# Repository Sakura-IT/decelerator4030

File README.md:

decelerator4030
===============

Decelerator 4030 CPU card for Amiga 3000/4000

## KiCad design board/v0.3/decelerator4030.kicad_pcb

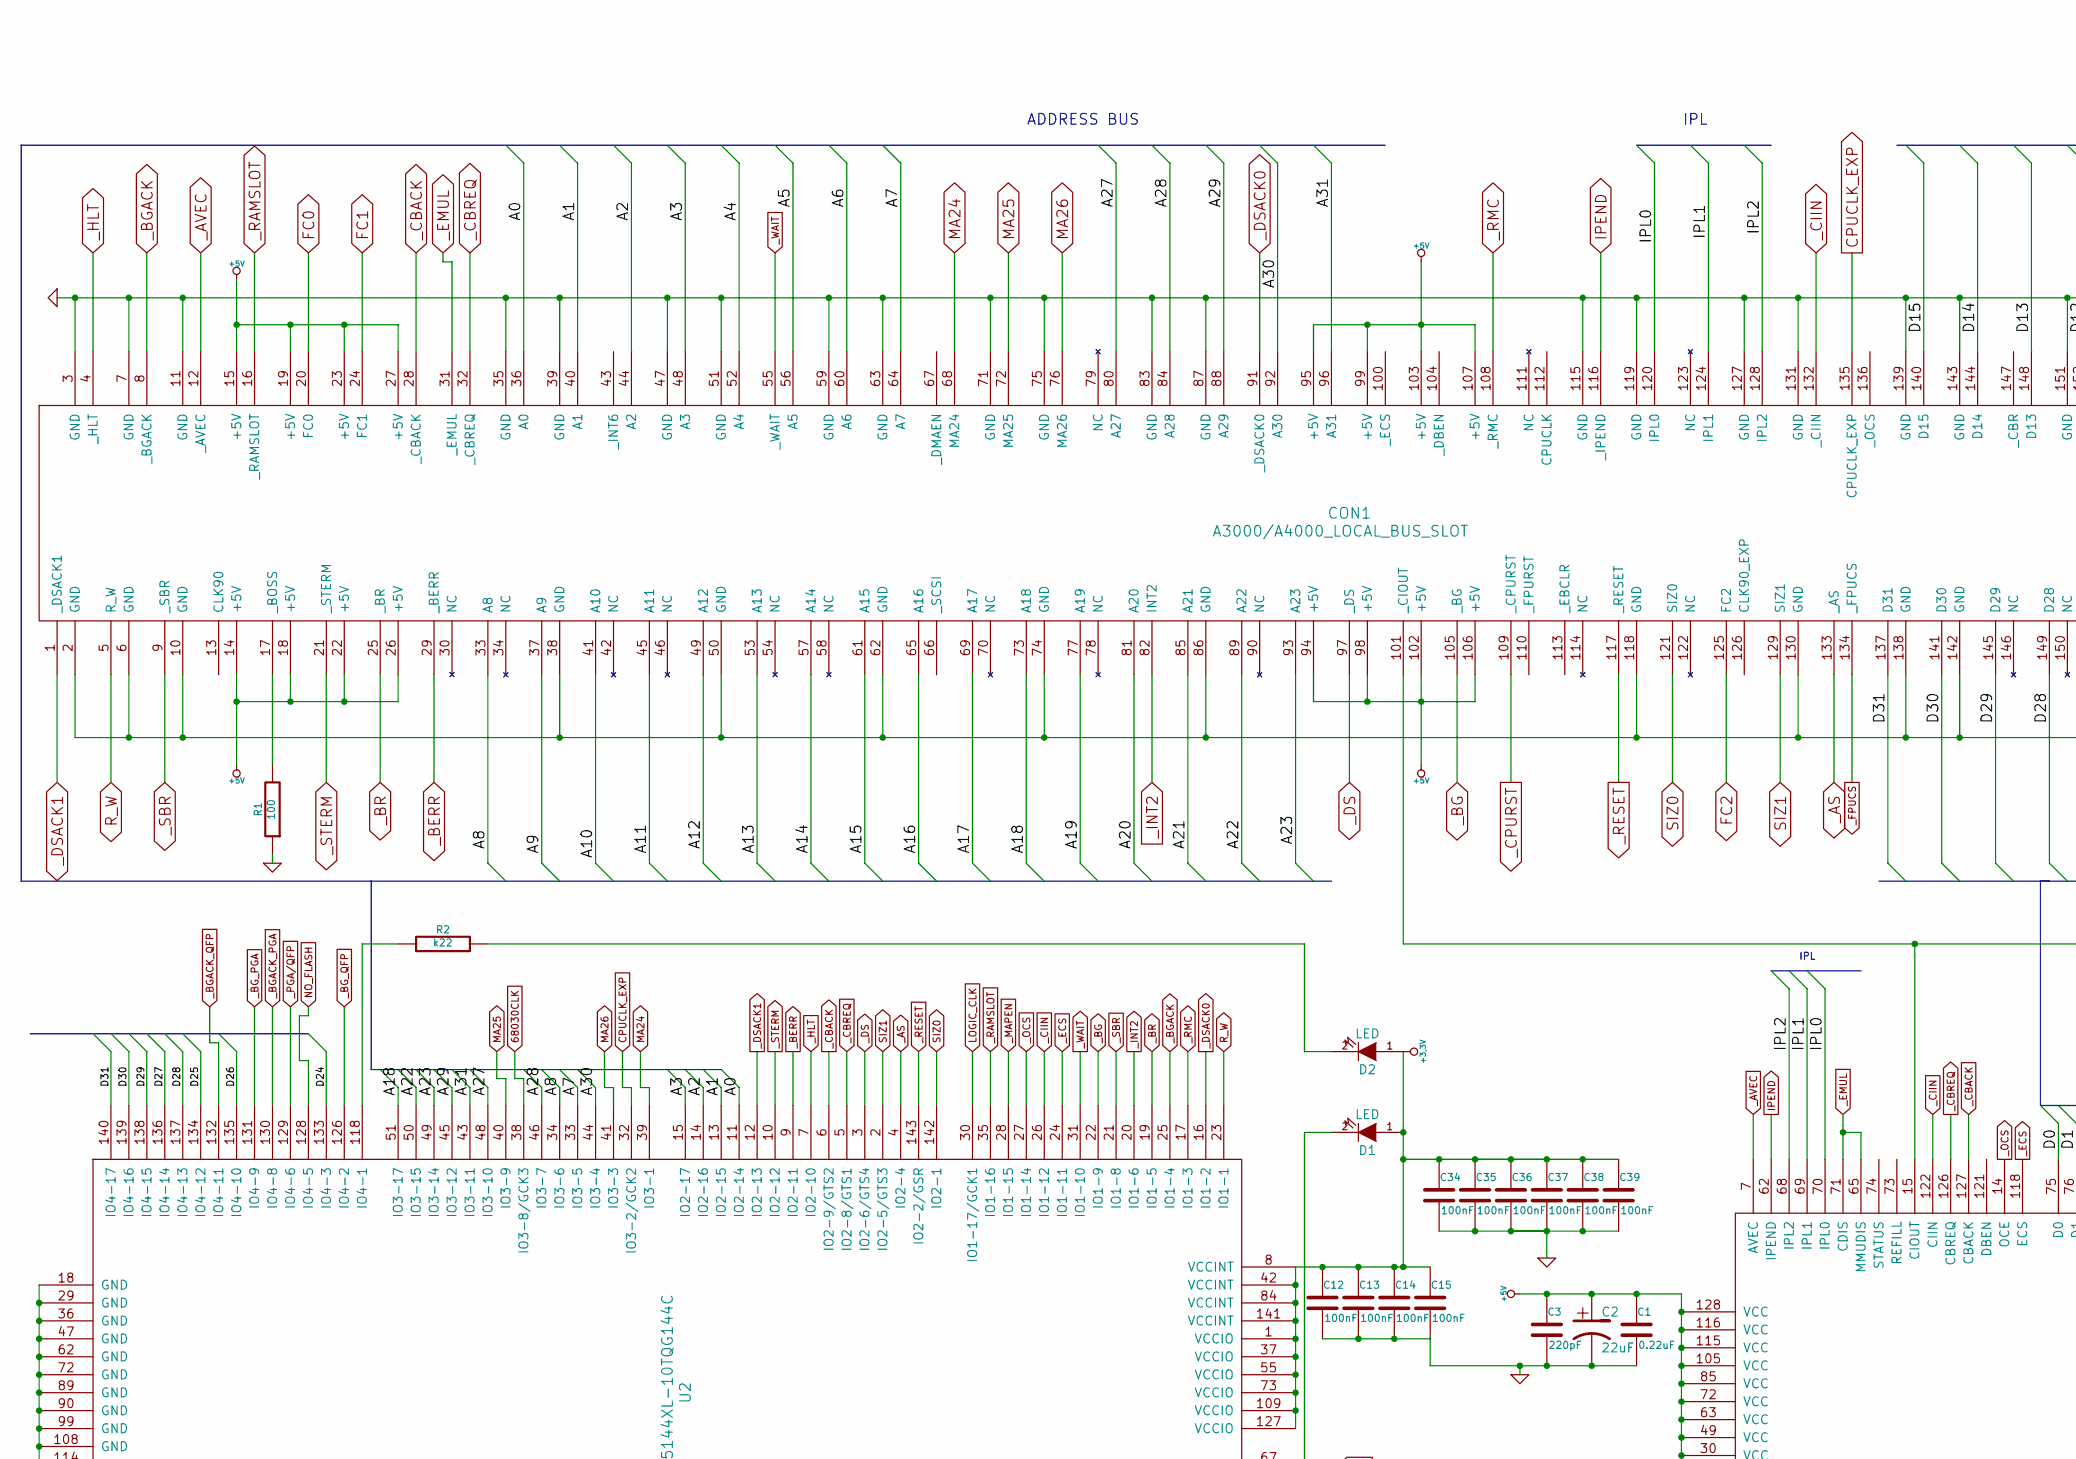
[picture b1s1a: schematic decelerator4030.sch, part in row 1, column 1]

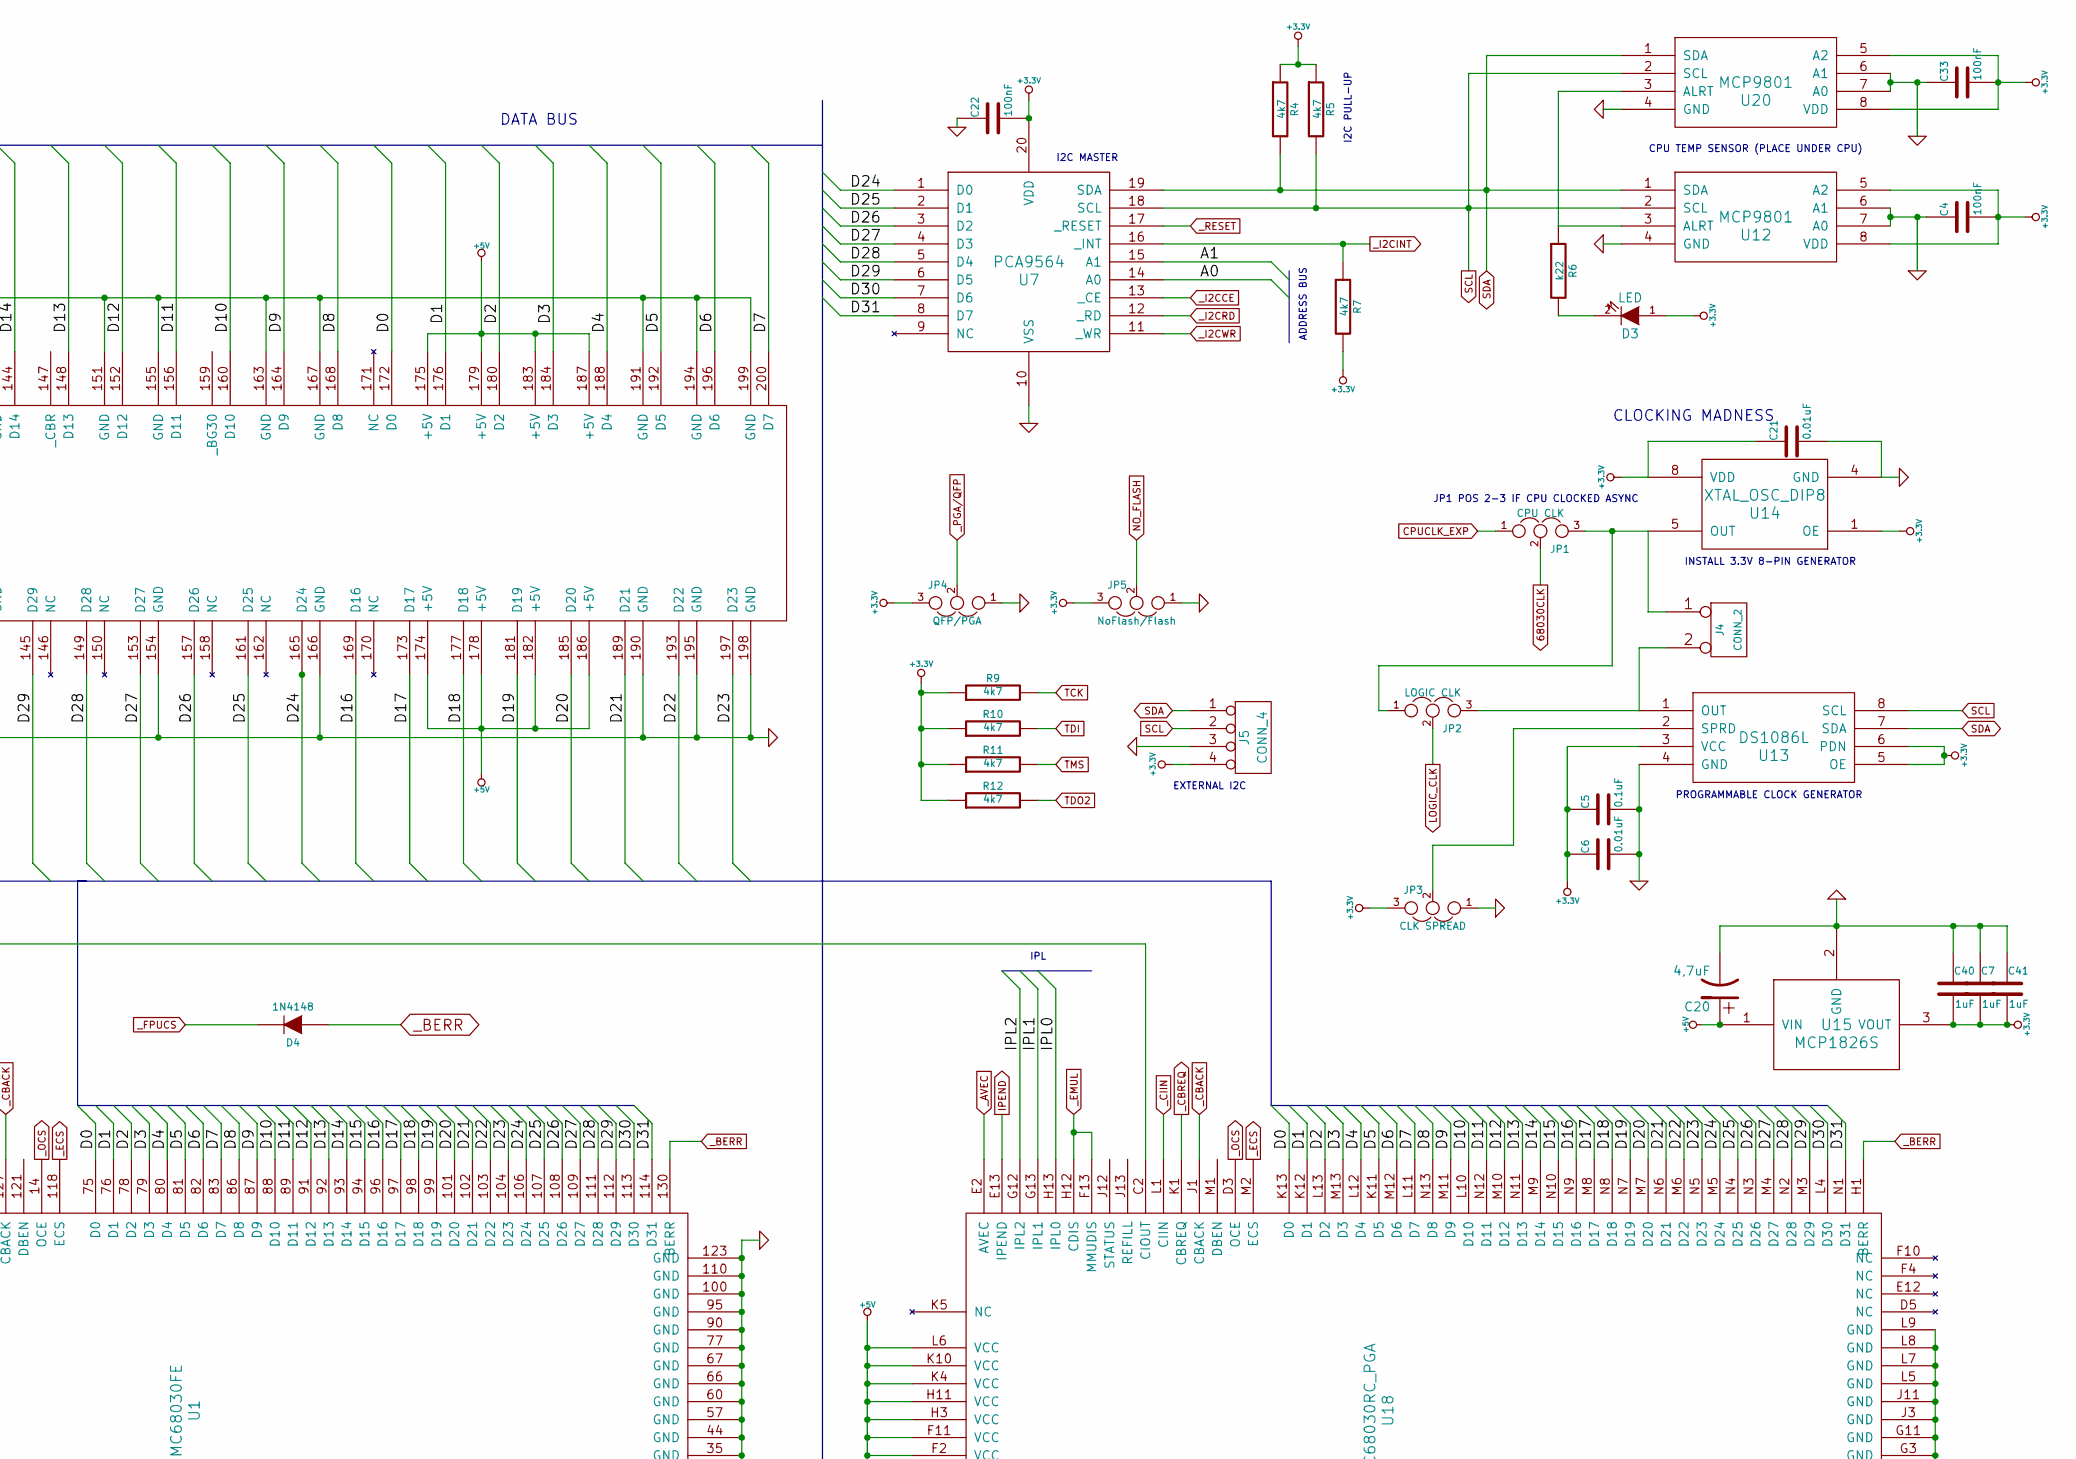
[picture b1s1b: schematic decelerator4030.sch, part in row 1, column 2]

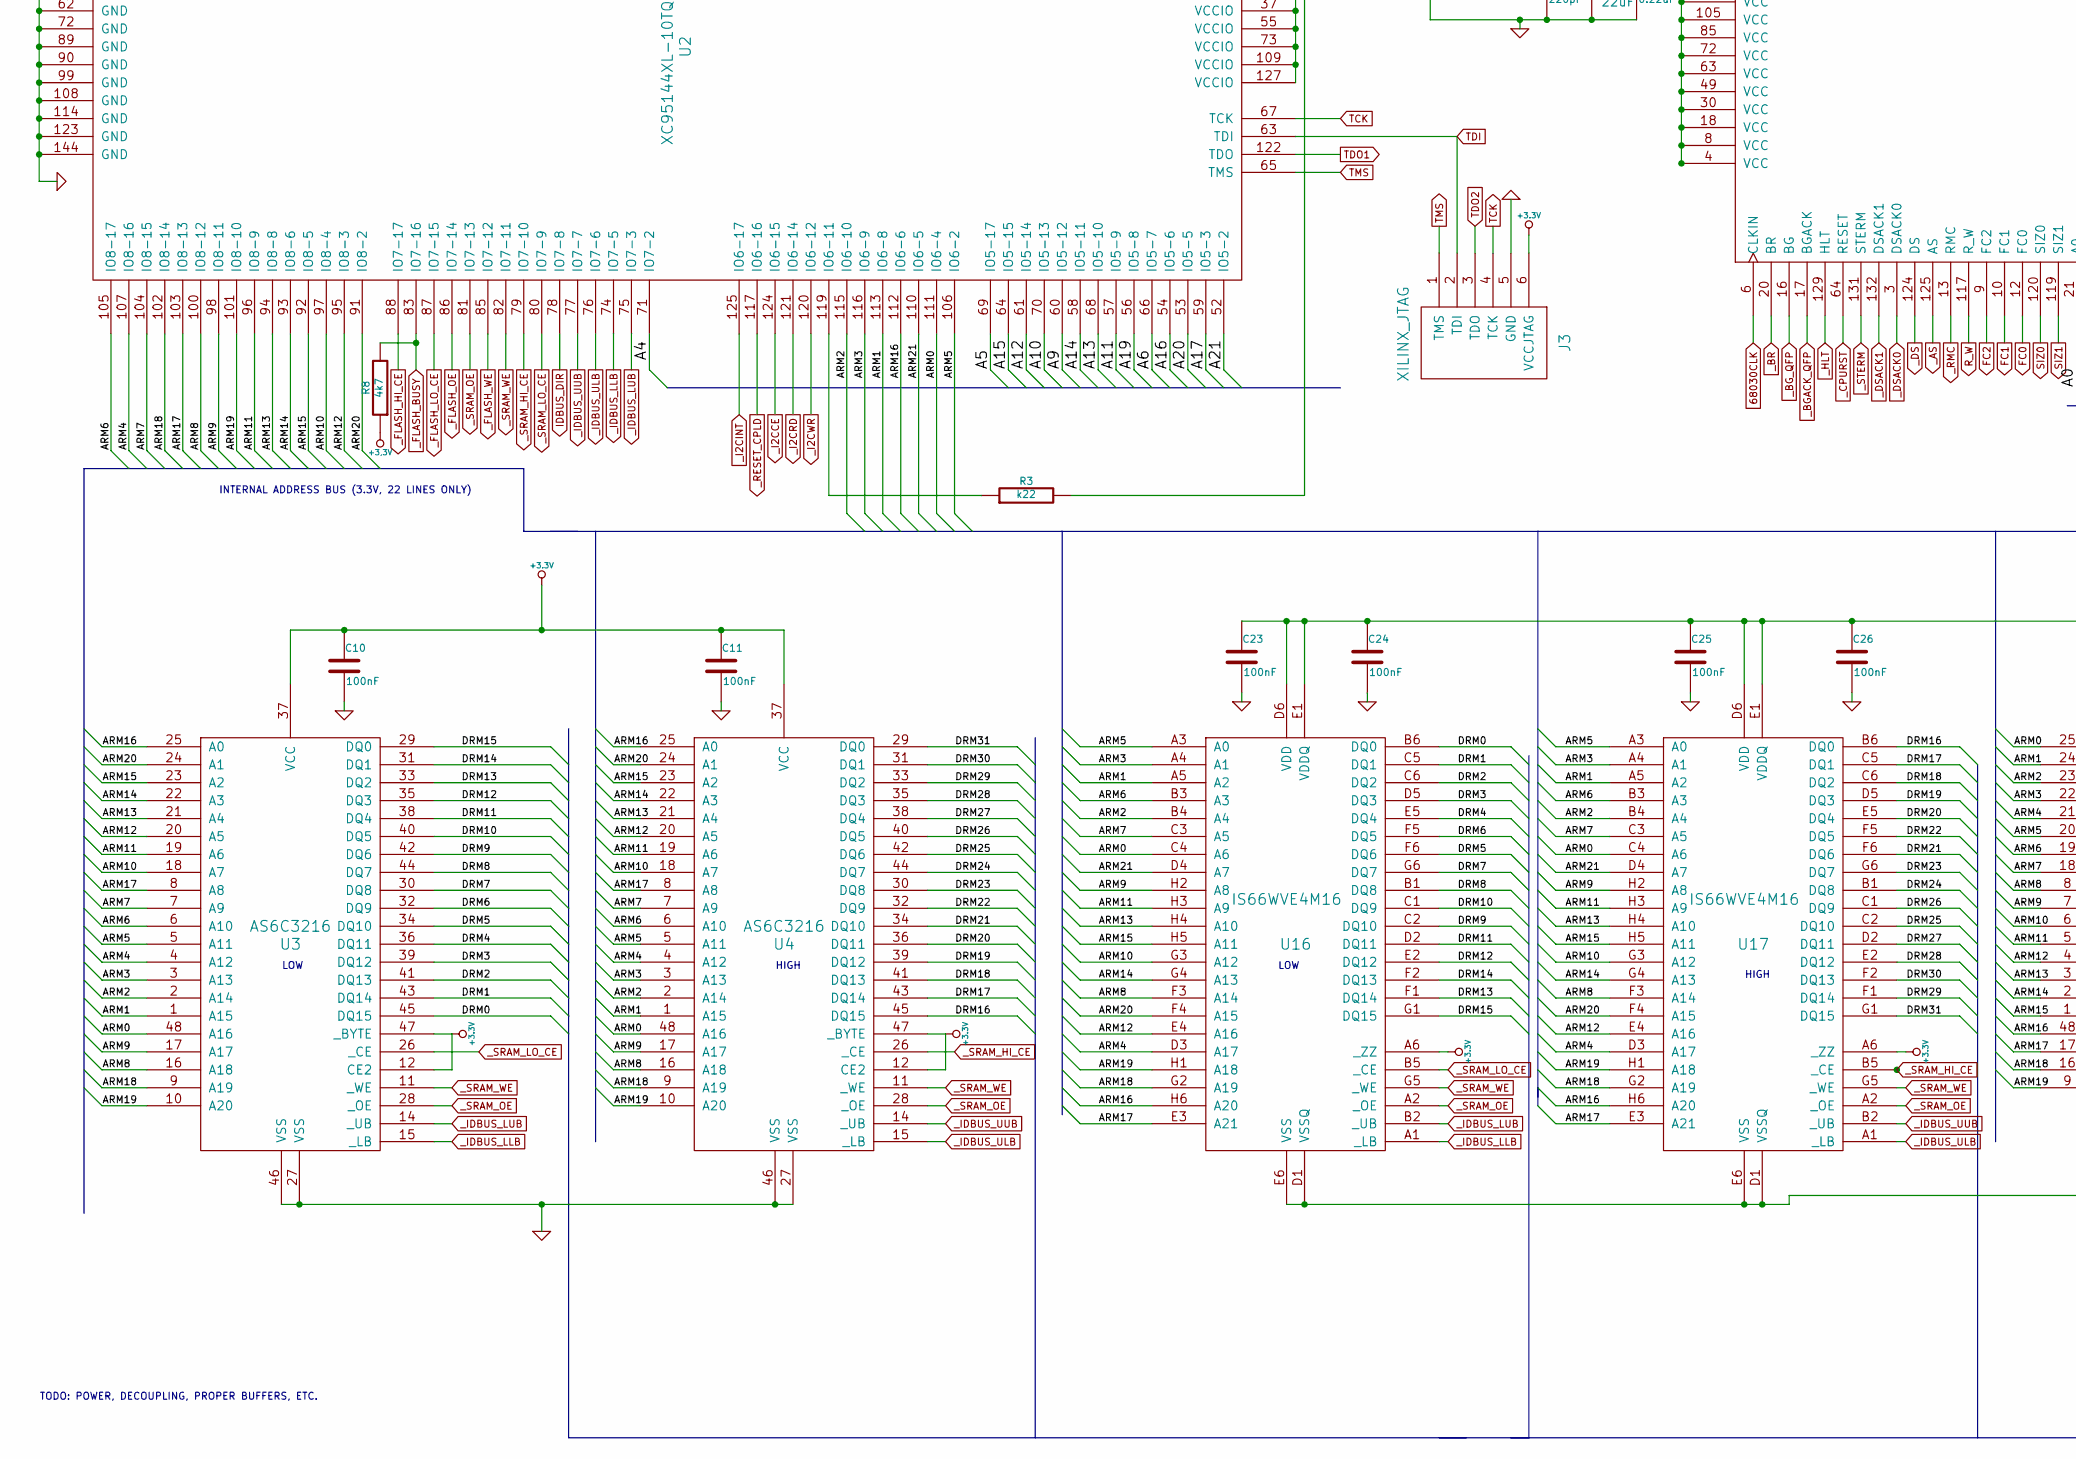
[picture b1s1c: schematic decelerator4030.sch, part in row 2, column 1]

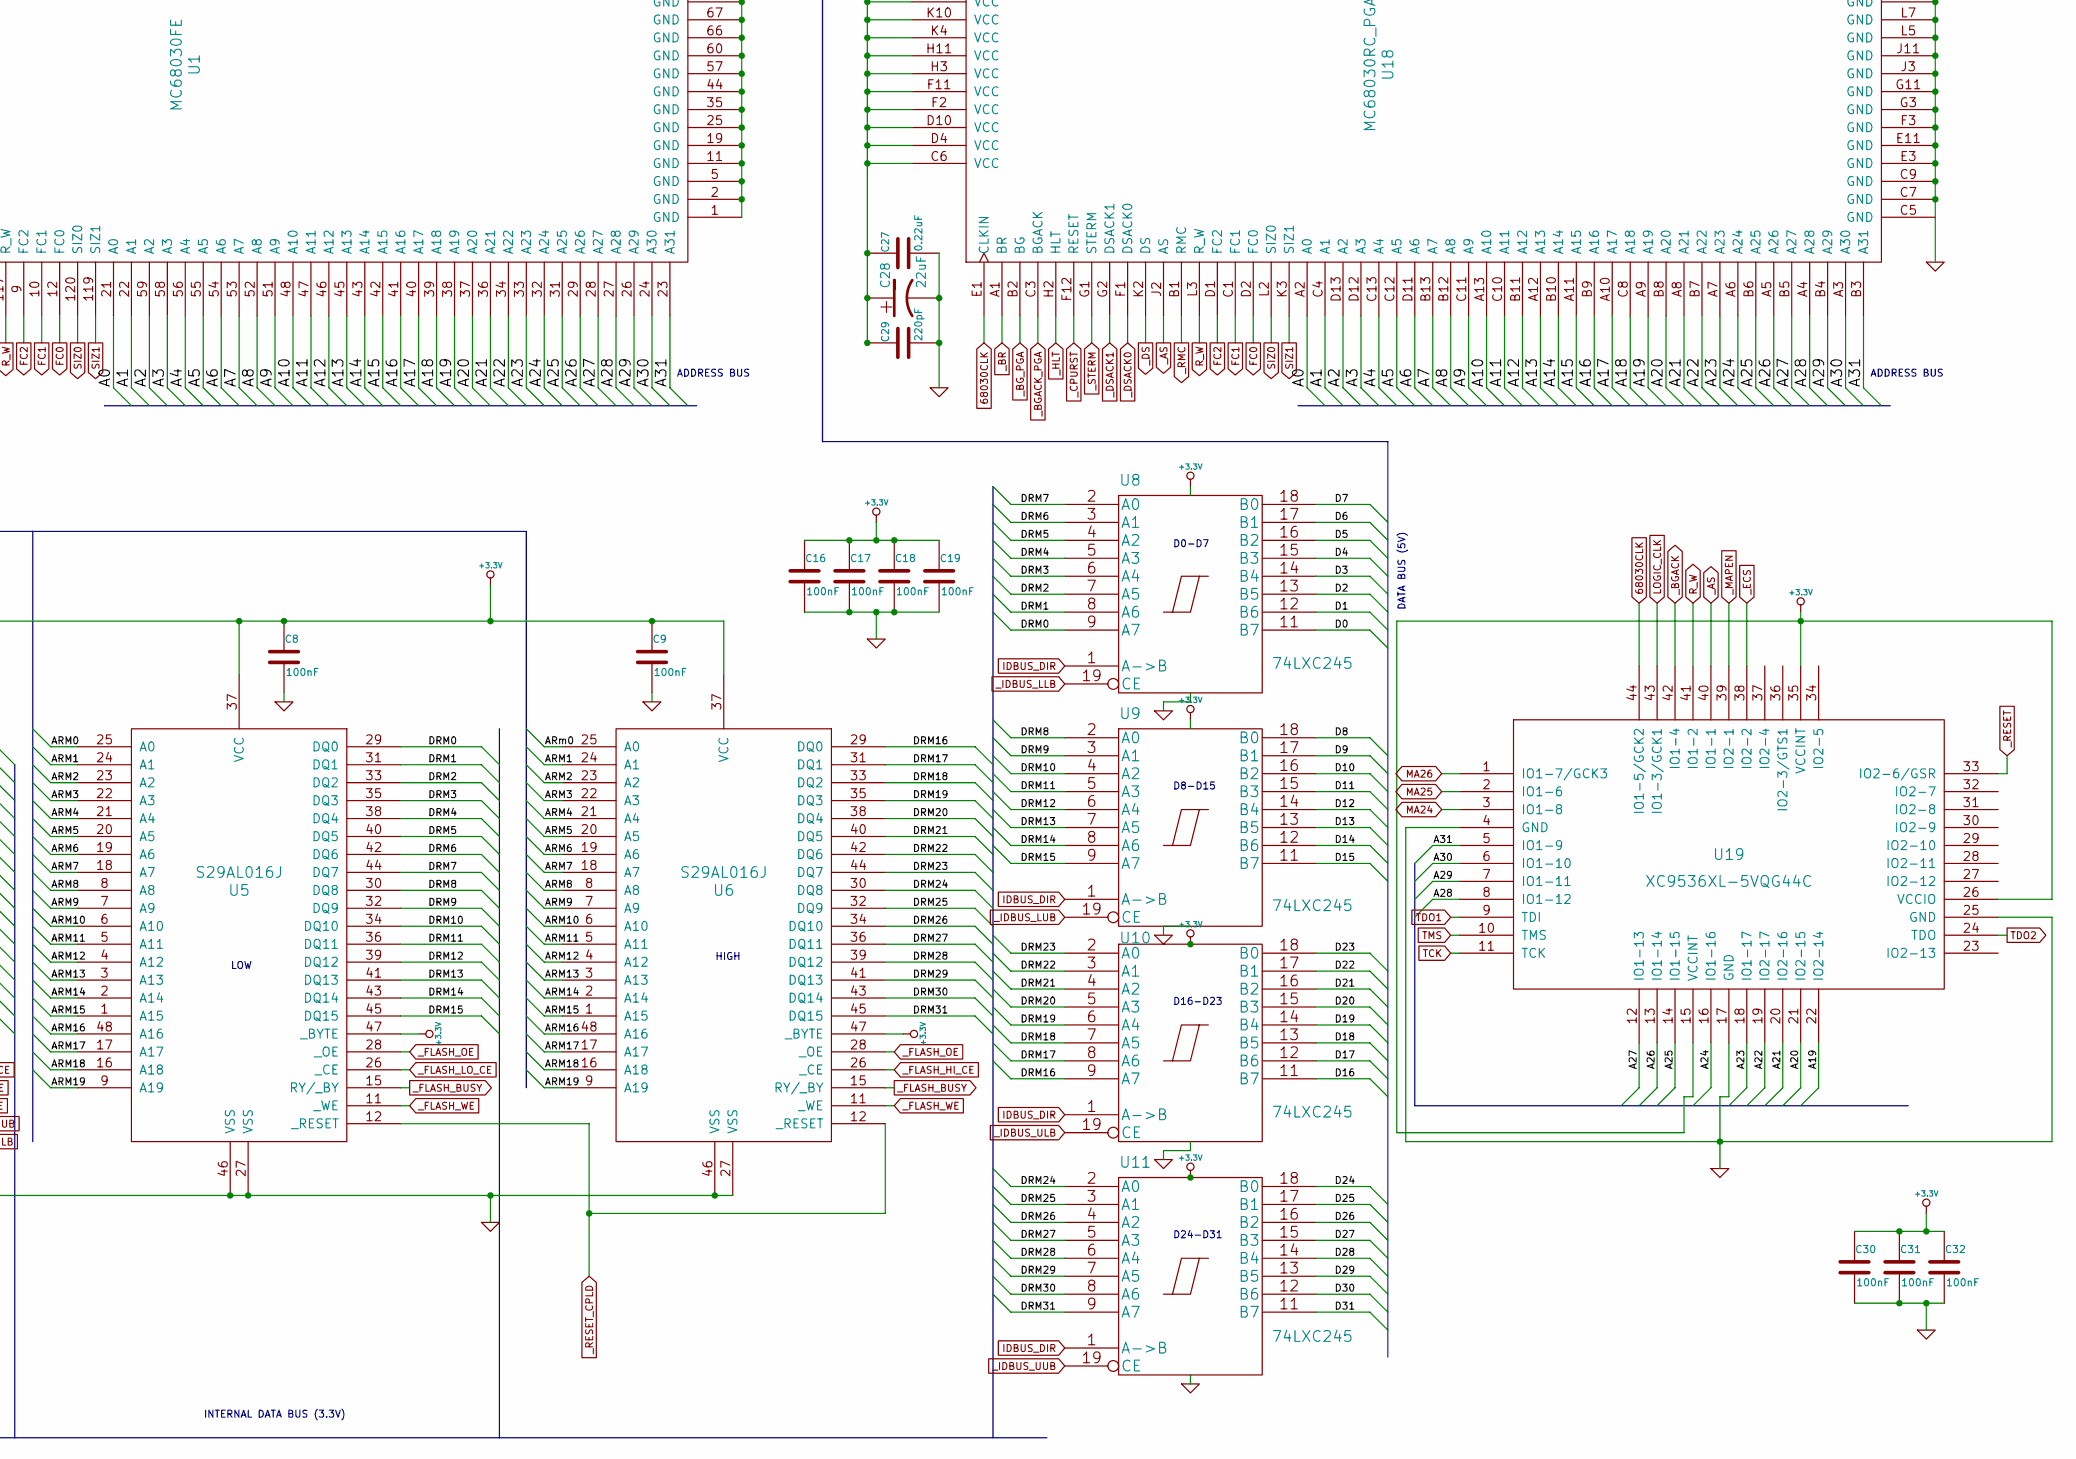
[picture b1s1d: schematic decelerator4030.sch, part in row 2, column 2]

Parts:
C1, C27: 0.22uF
C2, C28: 22uF
C3, C29: 220pF
C4, C8, C9, C10, C11, C12, C13, C14, C15, C16, C17, C18, C19, C22, C23, C24, C25, C26, C30, C31, C32, C33, C34, C35, C36, C37, C38, C39: 100nF
C5: 0.1uF
C6, C21: 0.01uF
C7, C40, C41: 1uF
C20: 4,7uF
CON1: A3000/A4000_LOCAL_BUS_SLOT
D1, D2, D3: LED
D4: 1N4148
J3: XILINX_JTAG
J4: CONN_2
J5: CONN_4
JP1: CPU CLK
JP2: LOGIC CLK
JP3: CLK SPREAD
JP4: QFP/PGA
JP5: NoFlash/Flash
R1: 100
R2, R3, R6: k22
R4, R5, R7, R8, R9, R10, R11, R12: 4k7
U1: MC68030FE
U2: XC95144XL-10TQG144C
U3, U4: AS6C3216
U5, U6: S29AL016J
U7: PCA9564
U8, U9, U10, U11: 74LXC245
U12, U20: MCP9801
U13: DS1086L
U14: XTAL_OSC_DIP8
U15: MCP1826S
U16, U17: IS66WVE4M16
U18: MC68030RC_PGA
U19: XC9536XL-5VQG44C

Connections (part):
68030CLK: JP1.2, U1.6 (CLKIN), U2.38 (IO3-8/GCK3), U18.E1 (CLKIN), U19.44 (IO1-5/GCK2)
+5V: C1.1, C2.1, C3.1, C20.1, C27.1, C28.1, C29.1, CON1.14 (+5V), CON1.15 (+5V), CON1.18 (+5V), CON1.19 (+5V), CON1.22 (+5V), CON1.23 (+5V), CON1.26 (+5V), CON1.27 (+5V), CON1.94 (+5V), CON1.95 (+5V), CON1.98 (+5V), CON1.99 (+5V), CON1.102 (+5V), CON1.103 (+5V), CON1.106 (+5V), CON1.107 (+5V), CON1.174 (+5V), CON1.175 (+5V), CON1.178 (+5V), CON1.179 (+5V), CON1.182 (+5V), CON1.183 (+5V), CON1.186 (+5V), CON1.187 (+5V), U1.4 (VCC), U1.8 (VCC), U1.18 (VCC), U1.30 (VCC), U1.49 (VCC), U1.63 (VCC), U1.72 (VCC), U1.85 (VCC), U1.105 (VCC), U1.115 (VCC), U1.116 (VCC), U1.128 (VCC), U15.1 (VIN), U18.C6 (VCC), U18.D4 (VCC), U18.D10 (VCC), U18.F2 (VCC), U18.F11 (VCC), U18.H3 (VCC), U18.H11 (VCC), U18.K4 (VCC), U18.K10 (VCC), U18.L6 (VCC)
/A0: CON1.36 (A0), U1.21 (A0), U2.11 (IO2-14), U7.14 (A0), U18.A2 (A0)
/A1: CON1.40 (A1), U1.22 (A1), U2.13 (IO2-15), U7.15 (A1), U18.C4 (A1)
/A2: CON1.44 (A2), U1.59 (A2), U2.14 (IO2-16), U18.D13 (A2)
/A3: CON1.48 (A3), U1.58 (A3), U2.15 (IO2-17), U18.D12 (A3)
/A4: CON1.52 (A4), U1.56 (A4), U2.71 (IO7-2), U18.C13 (A4)
/A5: CON1.56 (A5), U1.55 (A5), U2.69 (IO5-17), U18.C12 (A5)
/A6: CON1.60 (A6), U1.54 (A6), U2.66 (IO5-7), U18.D11 (A6)
/A7: CON1.64 (A7), U1.53 (A7), U2.33 (IO3-5), U18.B13 (A7)
/A8: CON1.33 (A8), U1.52 (A8), U2.34 (IO3-6), U18.B12 (A8)
/A9: CON1.37 (A9), U1.51 (A9), U2.60 (IO5-12), U18.C11 (A9)
/A10: CON1.41 (A10), U1.48 (A10), U2.70 (IO5-13), U18.A13 (A10)
/A11: CON1.45 (A11), U1.47 (A11), U2.57 (IO5-9), U18.C10 (A11)
/A12: CON1.49 (A12), U1.46 (A12), U2.61 (IO5-14), U18.B11 (A12)
/A13: CON1.53 (A13), U1.45 (A13), U2.68 (IO5-10), U18.A12 (A13)
/A14: CON1.57 (A14), U1.43 (A14), U2.58 (IO5-11), U18.B10 (A14)
/A15: CON1.61 (A15), U1.42 (A15), U2.64 (IO5-15), U18.A11 (A15)
/A16: CON1.65 (A16), U1.41 (A16), U2.54 (IO5-6), U18.B9 (A16)
/A17: CON1.69 (A17), U1.40 (A17), U2.59 (IO5-3), U18.A10 (A17)
/A18: CON1.73 (A18), U1.39 (A18), U2.51 (IO3-17), U18.C8 (A18)
/A19: CON1.77 (A19), U1.38 (A19), U2.56 (IO5-8), U18.A9 (A19), U19.22 (IO2-14)
/A20: CON1.81 (A20), U1.37 (A20), U2.53 (IO5-5), U18.B8 (A20), U19.21 (IO2-15)
/A21: CON1.85 (A21), U1.36 (A21), U2.52 (IO5-2), U18.A8 (A21), U19.20 (IO2-16)
/A22: CON1.89 (A22), U1.34 (A22), U2.50 (IO3-15), U18.B7 (A22), U19.19 (IO2-17)
/A23: CON1.93 (A23), U1.33 (A23), U2.49 (IO3-14), U18.A7 (A23), U19.18 (IO1-17)
/A24: U1.32 (A24), U18.A6 (A24), U19.16 (IO1-16)
/A25: U1.31 (A25), U18.B6 (A25), U19.14 (IO1-15)
/A26: U1.29 (A26), U18.A5 (A26), U19.13 (IO1-14)
/A27: CON1.80 (A27), U1.28 (A27), U2.48 (IO3-10), U18.B5 (A27), U19.12 (IO1-13)
/A28: CON1.84 (A28), U1.27 (A28), U2.46 (IO3-7), U18.A4 (A28), U19.8 (IO1-12)
/A29: CON1.88 (A29), U1.26 (A29), U2.45 (IO3-12), U18.B4 (A29), U19.7 (IO1-11)
/A30: CON1.92 (A30), U1.24 (A30), U2.44 (IO3-4), U18.A3 (A30), U19.6 (IO1-10)
/A31: CON1.96 (A31), U1.23 (A31), U2.43 (IO3-11), U18.B3 (A31), U19.5 (IO1-9)
/ARM0: U2.111 (IO6-4), U3.48 (A16), U4.48 (A16), U5.25 (A0), U6.25 (A0), U16.C4 (A6), U17.C4 (A6)
/ARM1: U2.113 (IO6-8), U3.1 (A15), U4.1 (A15), U5.24 (A1), U6.24 (A1), U16.A5 (A2), U17.A5 (A2)
/ARM2: U2.115 (IO6-10), U3.2 (A14), U4.2 (A14), U5.23 (A2), U6.23 (A2), U16.B4 (A4), U17.B4 (A4)
/ARM3: U2.116 (IO6-9), U3.3 (A13), U4.3 (A13), U5.22 (A3), U6.22 (A3), U16.A4 (A1), U17.A4 (A1)
/ARM4: U2.107 (IO8-16), U3.4 (A12), U4.4 (A12), U5.21 (A4), U6.21 (A4), U16.D3 (A17), U17.D3 (A17)
/ARM5: U2.106 (IO6-2), U3.5 (A11), U4.5 (A11), U5.20 (A5), U6.20 (A5), U16.A3 (A0), U17.A3 (A0)
/ARM6: U2.105 (IO8-17), U3.6 (A10), U4.6 (A10), U5.19 (A6), U6.19 (A6), U16.B3 (A3), U17.B3 (A3)
/ARM7: U2.104 (IO8-15), U3.7 (A9), U4.7 (A9), U5.18 (A7), U6.18 (A7), U16.C3 (A5), U17.C3 (A5)
/ARM8: U2.100 (IO8-12), U3.16 (A18), U4.16 (A18), U5.8 (A8), U6.8 (A8), U16.F3 (A14), U17.F3 (A14)
/ARM9: U2.98 (IO8-11), U3.17 (A17), U4.17 (A17), U5.7 (A9), U6.7 (A9), U16.H2 (A8), U17.H2 (A8)
/ARM10: U2.97 (IO8-4), U3.18 (A7), U4.18 (A7), U5.6 (A10), U6.6 (A10), U16.G3 (A12), U17.G3 (A12)
/ARM11: U2.96 (IO8-9), U3.19 (A6), U4.19 (A6), U5.5 (A11), U6.5 (A11), U16.H3 (A9), U17.H3 (A9)
/ARM12: U2.95 (IO8-3), U3.20 (A5), U4.20 (A5), U5.4 (A12), U6.4 (A12), U16.E4 (A16), U17.E4 (A16)
/ARM13: U2.94 (IO8-8), U3.21 (A4), U4.21 (A4), U5.3 (A13), U6.3 (A13), U16.H4 (A10), U17.H4 (A10)
/ARM14: U2.93 (IO8-6), U3.22 (A3), U4.22 (A3), U5.2 (A14), U6.2 (A14), U16.G4 (A13), U17.G4 (A13)
/ARM15: U2.92 (IO8-5), U3.23 (A2), U4.23 (A2), U5.1 (A15), U6.1 (A15), U16.H5 (A11), U17.H5 (A11)
/ARM16: U2.112 (IO6-6), U3.25 (A0), U4.25 (A0), U5.48 (A16), U6.48 (A16), U16.H6 (A20), U17.H6 (A20)
/ARM17: U2.103 (IO8-13), U3.8 (A8), U4.8 (A8), U5.17 (A17), U6.17 (A17), U16.E3 (A21), U17.E3 (A21)
/ARM18: U2.102 (IO8-14), U3.9 (A19), U4.9 (A19), U5.16 (A18), U6.16 (A18), U16.G2 (A19), U17.G2 (A19)
/ARM19: U2.101 (IO8-10), U3.10 (A20), U4.10 (A20), U5.9 (A19), U6.9 (A19), U16.H1 (A18), U17.H1 (A18)
/ARM20: U2.91 (IO8-2), U3.24 (A1), U4.24 (A1), U16.F4 (A15), U17.F4 (A15)
/ARM21: U2.110 (IO6-5), U16.D4 (A7), U17.D4 (A7)
/D0: CON1.172 (D0), U1.75 (D0), U8.11 (B7), U18.K13 (D0)
/D1: CON1.176 (D1), U1.76 (D1), U8.12 (B6), U18.K12 (D1)
/D2: CON1.180 (D2), U1.78 (D2), U8.13 (B5), U18.L13 (D2)
/D3: CON1.184 (D3), U1.79 (D3), U8.14 (B4), U18.M13 (D3)
/D4: CON1.188 (D4), U1.80 (D4), U8.15 (B3), U18.L12 (D4)
/D5: CON1.192 (D5), U1.81 (D5), U8.16 (B2), U18.K11 (D5)
/D6: CON1.196 (D6), U1.82 (D6), U8.17 (B1), U18.M12 (D6)
/D7: CON1.200 (D7), U1.83 (D7), U8.18 (B0), U18.L11 (D7)
/D8: CON1.168 (D8), U1.86 (D8), U9.18 (B0), U18.N13 (D8)
/D9: CON1.164 (D9), U1.87 (D9), U9.17 (B1), U18.M11 (D9)
/D10: CON1.160 (D10), U1.88 (D10), U9.16 (B2), U18.L10 (D10)
/D11: CON1.156 (D11), U1.89 (D11), U9.15 (B3), U18.N12 (D11)
/D12: CON1.152 (D12), U1.91 (D12), U9.14 (B4), U18.M10 (D12)
/D13: CON1.148 (D13), U1.92 (D13), U9.13 (B5), U18.N11 (D13)
/D14: CON1.144 (D14), U1.93 (D14), U9.12 (B6), U18.M9 (D14)
/D15: CON1.140 (D15), U1.94 (D15), U9.11 (B7), U18.N10 (D15)
/D16: CON1.169 (D16), U1.96 (D16), U10.11 (B7), U18.N9 (D16)
/D17: CON1.173 (D17), U1.97 (D17), U10.12 (B6), U18.M8 (D17)
/D18: CON1.177 (D18), U1.98 (D18), U10.13 (B5), U18.N8 (D18)
/D19: CON1.181 (D19), U1.99 (D19), U10.14 (B4), U18.N7 (D19)
/D20: CON1.185 (D20), U1.101 (D20), U10.15 (B3), U18.M7 (D20)
/D21: CON1.189 (D21), U1.102 (D21), U10.16 (B2), U18.N6 (D21)
/D22: CON1.193 (D22), U1.103 (D22), U10.17 (B1), U18.M6 (D22)
/D23: CON1.197 (D23), U1.104 (D23), U10.18 (B0), U18.N5 (D23)
/D24: CON1.165 (D24), U1.106 (D24), U2.133 (IO4-3), U7.1 (D0), U11.18 (B0), U18.M5 (D24)
/D25: CON1.161 (D25), U1.107 (D25), U2.134 (IO4-12), U7.2 (D1), U11.17 (B1), U18.N4 (D25)
/D26: CON1.157 (D26), U1.108 (D26), U2.135 (IO4-10), U7.3 (D2), U11.16 (B2), U18.N3 (D26)
/D27: CON1.153 (D27), U1.109 (D27), U2.136 (IO4-14), U7.4 (D3), U11.15 (B3), U18.M4 (D27)
/D28: CON1.149 (D28), U1.111 (D28), U2.137 (IO4-13), U7.5 (D4), U11.14 (B4), U18.N2 (D28)
/D29: CON1.145 (D29), U1.112 (D29), U2.138 (IO4-15), U7.6 (D5), U11.13 (B5), U18.M3 (D29)
/D30: CON1.141 (D30), U1.113 (D30), U2.139 (IO4-16), U7.7 (D6), U11.12 (B6), U18.L4 (D30)
/D31: CON1.137 (D31), U1.114 (D31), U2.140 (IO4-17), U7.8 (D7), U11.11 (B7), U18.N1 (D31)
/DRM0: U3.45 (DQ15), U5.29 (DQ0), U8.9 (A7), U16.B6 (DQ0)
/DRM1: U3.43 (DQ14), U5.31 (DQ1), U8.8 (A6), U16.C5 (DQ1)
/DRM2: U3.41 (DQ13), U5.33 (DQ2), U8.7 (A5), U16.C6 (DQ2)
/DRM3: U3.39 (DQ12), U5.35 (DQ3), U8.6 (A4), U16.D5 (DQ3)
/DRM4: U3.36 (DQ11), U5.38 (DQ4), U8.5 (A3), U16.E5 (DQ4)
/DRM5: U3.34 (DQ10), U5.40 (DQ5), U8.4 (A2), U16.F6 (DQ6)
/DRM6: U3.32 (DQ9), U5.42 (DQ6), U8.3 (A1), U16.F5 (DQ5)
/DRM7: U3.30 (DQ8), U5.44 (DQ7), U8.2 (A0), U16.G6 (DQ7)
/DRM8: U3.44 (DQ7), U5.30 (DQ8), U9.2 (A0), U16.B1 (DQ8)
/DRM9: U3.42 (DQ6), U5.32 (DQ9), U9.3 (A1), U16.C2 (DQ10)
/DRM10: U3.40 (DQ5), U5.34 (DQ10), U9.4 (A2), U16.C1 (DQ9)
/DRM11: U3.38 (DQ4), U5.36 (DQ11), U9.5 (A3), U16.D2 (DQ11)
/DRM12: U3.35 (DQ3), U5.39 (DQ12), U9.6 (A4), U16.E2 (DQ12)
/DRM13: U3.33 (DQ2), U5.41 (DQ13), U9.7 (A5), U16.F1 (DQ14)
/DRM14: U3.31 (DQ1), U5.43 (DQ14), U9.8 (A6), U16.F2 (DQ13)
/DRM15: U3.29 (DQ0), U5.45 (DQ15), U9.9 (A7), U16.G1 (DQ15)
/DRM16: U4.45 (DQ15), U6.29 (DQ0), U10.9 (A7), U17.B6 (DQ0)
/DRM17: U4.43 (DQ14), U6.31 (DQ1), U10.8 (A6), U17.C5 (DQ1)
/DRM18: U4.41 (DQ13), U6.33 (DQ2), U10.7 (A5), U17.C6 (DQ2)
/DRM19: U4.39 (DQ12), U6.35 (DQ3), U10.6 (A4), U17.D5 (DQ3)
/DRM20: U4.36 (DQ11), U6.38 (DQ4), U10.5 (A3), U17.E5 (DQ4)
/DRM21: U4.34 (DQ10), U6.40 (DQ5), U10.4 (A2), U17.F6 (DQ6)
/DRM22: U4.32 (DQ9), U6.42 (DQ6), U10.3 (A1), U17.F5 (DQ5)
/DRM23: U4.30 (DQ8), U6.44 (DQ7), U10.2 (A0), U17.G6 (DQ7)
/DRM24: U4.44 (DQ7), U6.30 (DQ8), U11.2 (A0), U17.B1 (DQ8)
/DRM25: U4.42 (DQ6), U6.32 (DQ9), U11.3 (A1), U17.C2 (DQ10)
/DRM26: U4.40 (DQ5), U6.34 (DQ10), U11.4 (A2), U17.C1 (DQ9)
/DRM27: U4.38 (DQ4), U6.36 (DQ11), U11.5 (A3), U17.D2 (DQ11)
/DRM28: U4.35 (DQ3), U6.39 (DQ12), U11.6 (A4), U17.E2 (DQ12)
/DRM29: U4.33 (DQ2), U6.41 (DQ13), U11.7 (A5), U17.F1 (DQ14)
/DRM30: U4.31 (DQ1), U6.43 (DQ14), U11.8 (A6), U17.F2 (DQ13)
/DRM31: U4.29 (DQ0), U6.45 (DQ15), U11.9 (A7), U17.G1 (DQ15)
/IPL0: CON1.120 (IPL0), U1.70 (IPL0), U18.H13 (IPL0)
/IPL1: CON1.124 (IPL1), U1.69 (IPL1), U18.G13 (IPL1)
/IPL2: CON1.128 (IPL2), U1.68 (IPL2), U18.G12 (IPL2)
CPUCLK_EXP: CON1.135 (CPUCLK_EXP), JP1.1, U2.32 (IO3-2/GCK2)
FC0: CON1.20 (FC0), U1.12 (FC0), U18.D2 (FC0)
FC1: CON1.24 (FC1), U1.10 (FC1), U18.C1 (FC1)
FC2: CON1.125 (FC2), U1.9 (FC2), U18.D1 (FC2)
GND: C1.2, C2.2, C3.2, C4.1, C5.2, C6.2, C7.1, C8.2, C9.2, C10.2, C11.2, C12.2, C13.2, C14.2, C15.2, C16.2, C17.2, C18.2, C19.2, C20.2, C21.2, C22.1, C23.2, C24.2, C25.2, C26.2, C27.2, C28.2, C29.2, C30.2, C31.2, C32.2, C33.1, C34.2, C35.2, C36.2, C37.2, C38.2, C39.2, C40.1, C41.1, CON1.2 (GND), CON1.3 (GND), CON1.6 (GND), CON1.7 (GND), CON1.10 (GND), CON1.11 (GND), CON1.35 (GND), CON1.38 (GND), CON1.39 (GND), CON1.47 (GND), CON1.50 (GND), CON1.51 (GND), CON1.59 (GND), CON1.62 (GND), CON1.63 (GND), CON1.71 (GND), CON1.74 (GND), CON1.75 (GND), CON1.83 (GND), CON1.86 (GND), CON1.87 (GND), CON1.115 (GND), CON1.118 (GND), CON1.119 (GND), CON1.127 (GND), CON1.130 (GND), CON1.131 (GND), CON1.138 (GND), CON1.139 (GND), CON1.142 (GND), CON1.143 (GND), CON1.151 (GND), CON1.154 (GND), CON1.155 (GND), CON1.163 (GND), CON1.166 (GND), CON1.167 (GND), CON1.190 (GND), CON1.191 (GND)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; also elsewhere on the board
IDBUS_DIR: U2.78 (IO7-8), U8.1 (A->B), U9.1 (A->B), U10.1 (A->B), U11.1 (A->B)
IPEND: CON1.116 (_IPEND), U1.62 (IPEND), U18.E13 (IPEND)
LOGIC_CLK: JP2.2, U2.30 (IO1-17/GCK1), U19.43 (IO1-3/GCK1)
MA24: CON1.68 (MA24), U2.39 (IO3-1), U19.3 (IO1-8)
MA25: CON1.72 (MA25), U2.40 (IO3-9), U19.2 (IO1-6)
MA26: CON1.76 (MA26), U2.41 (IO3-3), U19.1 (IO1-7/GCK3)
unnamed: CON1.17 (_BOSS), R1.2
unnamed: CON1.101 (_CIOUT), U1.15 (CIOUT), U18.C2 (CIOUT)
unnamed: R2.1, U2.118 (IO4-1)
unnamed: D2.2 (K), R2.2
unnamed: R3.1, U2.119 (IO6-11)
unnamed: D1.2 (K), R3.2
unnamed: R6.1, U12.3 (ALRT), U20.3 (ALRT)
unnamed: J4.1, JP1.3, JP2.1, U14.5 (OUT)
unnamed: J4.2 (PM), JP2.3, U13.1 (OUT)
unnamed: JP3.2, U13.2 (SPRD)
unnamed: D3.2 (K), R6.2
NO_FLASH: JP5.2, U2.128 (IO4-5)
R_W: CON1.5 (R_W), U1.117 (R_W), U2.23 (IO1-1), U18.L3 (R_W), U19.41 (IO1-2)
SCL: J5.2, R5.2, U7.18 (SCL), U12.2 (SCL), U13.8 (SCL), U20.2 (SCL)
SDA: J5.1, R4.2, U7.19 (SDA), U12.1 (SDA), U13.7 (SDA), U20.1 (SDA)
SIZ0: CON1.121 (SIZ0), U1.120 (SIZ0), U2.142 (IO2-1), U18.L2 (SIZ0)
SIZ1: CON1.129 (SIZ1), U1.119 (SIZ1), U2.2 (IO2-5/GTS3), U18.K3 (SIZ1)
TCK: J3.4 (TCK), R9.2, U2.67 (TCK), U19.11 (TCK)
TDI: J3.2 (TDI), R10.2, U2.63 (TDI)
TDO1: U2.122 (TDO), U19.9 (TDI)
TDO2: J3.3 (TDO), R12.2, U19.24 (TDO)
TMS: J3.1 (TMS), R11.2, U2.65 (TMS), U19.10 (TMS)
_AS: CON1.133 (_AS), U1.125 (AS), U2.4 (IO2-4), U18.J2 (AS), U19.40 (IO1-1)
_AVEC: CON1.12 (_AVEC), U1.7 (AVEC), U18.E2 (AVEC)
_BERR: CON1.29 (_BERR), D4.2 (A), U1.130 (BERR), U2.9 (IO2-11), U18.H1 (BERR)
_BG: CON1.105 (_BG), U2.22 (IO1-9)
_BGACK: CON1.8 (_BGACK), U2.25 (IO1-4), U19.42 (IO1-4)
_BGACK_PGA: U2.130 (IO4-8), U18.C3 (BGACK)
_BGACK_QFP: U1.17 (BGACK), U2.132 (IO4-11)
_BG_PGA: U2.131 (IO4-9), U18.B2 (BG)
_BG_QFP: U1.16 (BG), U2.126 (IO4-2)
_BR: CON1.25 (_BR), U1.20 (BR), U2.19 (IO1-5), U18.A1 (BR)
_CBACK: CON1.28 (_CBACK), U1.127 (CBACK), U2.6 (IO2-9/GTS2), U18.J1 (CBACK)
_CBREQ: CON1.32 (_CBREQ), U1.126 (CBREQ), U2.5 (IO2-8/GTS1), U18.K1 (CBREQ)
_CIIN: CON1.132 (_CIIN), U1.122 (CIIN), U2.26 (IO1-12), U18.L1 (CIIN)
_CPURST: CON1.109 (_CPURST), U1.64 (RESET), U18.F12 (RESET)
_DS: CON1.97 (_DS), U1.124 (DS), U2.3 (IO2-6/GTS4), U18.K2 (DS)
_DSACK0: CON1.91 (_DSACK0), U1.3 (DSACK0), U2.16 (IO1-2), U18.F1 (DSACK0)
_DSACK1: CON1.1 (_DSACK1), U1.132 (DSACK1), U2.12 (IO2-13), U18.G2 (DSACK1)
_ECS: U1.118 (ECS), U2.24 (IO1-11), U18.M2 (ECS), U19.38 (IO2-2)
_EMUL: CON1.31 (_EMUL), U1.65 (MMUDIS), U1.71 (CDIS), U18.F13 (MMUDIS), U18.H12 (CDIS)
_FLASH_BUSY: R8.2, U2.83 (IO7-16), U5.15 (RY/_BY), U6.15 (RY/_BY)
_FLASH_HI_CE: U2.88 (IO7-17), U6.26 (_CE)
_FLASH_LO_CE: U2.87 (IO7-15), U5.26 (_CE)
_FLASH_OE: U2.86 (IO7-14), U5.28 (_OE), U6.28 (_OE)
_FLASH_WE: U2.85 (IO7-12), U5.11 (_WE), U6.11 (_WE)
_FPUCS: CON1.134 (_FPUCS), D4.1 (K)
_HLT: CON1.4 (_HLT), U1.129 (HLT), U2.7 (IO2-10), U18.H2 (HLT)
_I2CCE: U2.124 (IO6-15), U7.13 (_CE)
_I2CINT: R7.1, U2.125 (IO6-17), U7.16 (_INT)
_I2CRD: U2.121 (IO6-14), U7.12 (_RD)
_I2CWR: U2.120 (IO6-12), U7.11 (_WR)
_IDBUS_LLB: U2.74 (IO7-5), U3.15 (_LB), U8.19 (CE), U16.A1 (_LB)
_IDBUS_LUB: U2.75 (IO7-3), U3.14 (_UB), U9.19 (CE), U16.B2 (_UB)
_IDBUS_ULB: U2.76 (IO7-6), U4.15 (_LB), U10.19 (CE), U17.A1 (_LB)
_IDBUS_UUB: U2.77 (IO7-7), U4.14 (_UB), U11.19 (CE), U17.B2 (_UB)
_INT2: CON1.82 (INT2), U2.20 (IO1-6)
_MAPEN: U2.28 (IO1-15), U19.39 (IO2-1)
_OCS: U1.14 (OCE), U2.27 (IO1-14), U18.D3 (OCE)
_PGA/QFP: JP4.2, U2.129 (IO4-6)
_RAMSLOT: CON1.16 (_RAMSLOT), U2.35 (IO1-16)
_RESET: CON1.117 (_RESET), U2.143 (IO2-2/GSR), U7.17 (_RESET), U19.33 (IO2-6/GSR)
_RESET_CPLD: U2.117 (IO6-16), U5.12 (_RESET), U6.12 (_RESET)
_RMC: CON1.108 (_RMC), U1.13 (RMC), U2.17 (IO1-3), U18.B1 (RMC)
_SBR: CON1.9 (_SBR), U2.21 (IO1-8)
_SRAM_HI_CE: U2.79 (IO7-10), U4.26 (_CE), U17.B5 (_CE)
_SRAM_LO_CE: U2.80 (IO7-9), U3.26 (_CE), U16.B5 (_CE)
_SRAM_OE: U2.81 (IO7-13), U3.28 (_OE), U4.28 (_OE), U16.A2 (_OE), U17.A2 (_OE)
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
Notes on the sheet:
DATA BUS
ADDRESS BUS
IPL
ADDRESS BUS
INTERNAL ADDRESS BUS (3.3V, 22 LINES ONLY)
CLOCKING MADNESS
LOW
HIGH
INTERNAL DATA BUS (3.3V)
D0-D7
D8-D15
DATA BUS (5V)
D16-D23
D24-D31
TODO: POWER, DECOUPLING, PROPER BUFFERS, ETC.
I2C MASTER
I2C PULL-UP
CPU TEMP SENSOR (PLACE UNDER CPU)
INSTALL 3.3V 8-PIN GENERATOR
PROGRAMMABLE CLOCK GENERATOR
JP1 POS 2-3 IF CPU CLOCKED ASYNC
EXTERNAL I2C

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
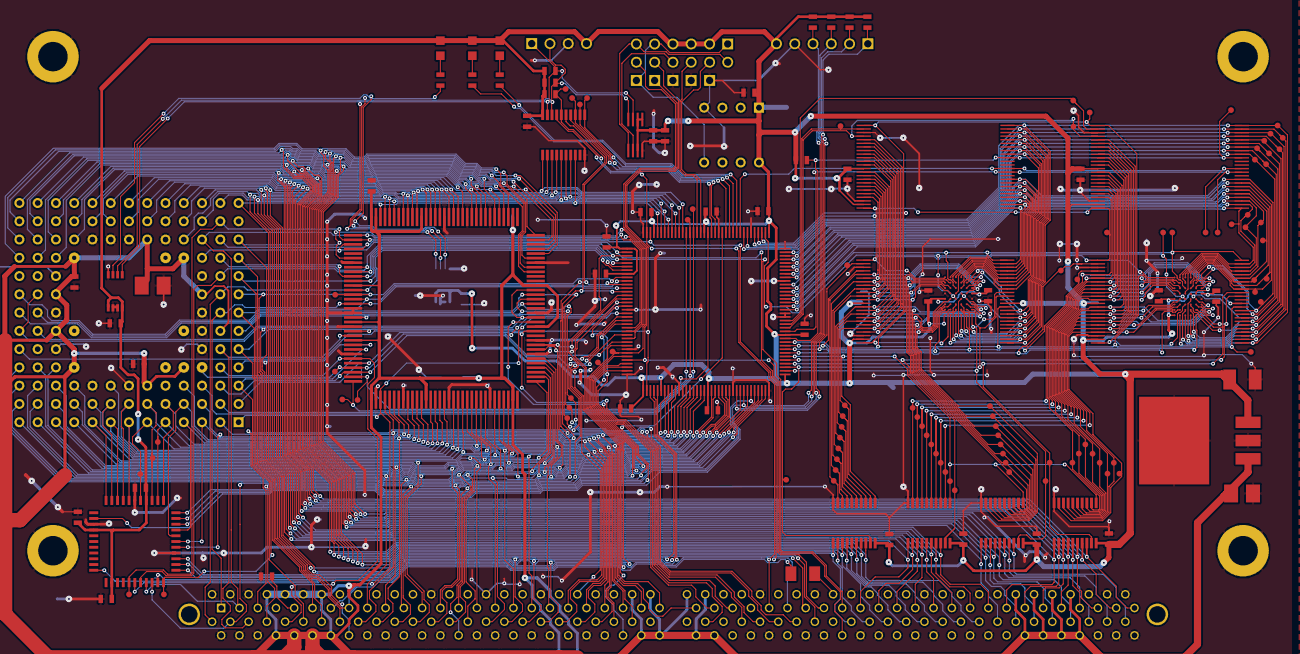
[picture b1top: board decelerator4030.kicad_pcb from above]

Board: 2 copper layers, 90 parts (0 on the bottom side), 206 nets.

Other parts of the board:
Hole_4mm, Hole_4mm#2, Hole_4mm#3, Hole_4mm#4: P***; hole_4mm

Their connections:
GND: Hole_4mm.1, Hole_4mm#2.1, Hole_4mm#3.1, Hole_4mm#4.1; also elsewhere on the board

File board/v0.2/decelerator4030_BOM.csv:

"Id";"Oznaczenie";"Obudowa";"Ilość";"Oznaczenie";"Dostawca i numer artykułu";
1;"U17,U16";"tfbga48";2;"IS66WVE4M16";;;
2;"U18";"MC68030RC_PGA";1;"MC68030RC_PGA";;;
3;"U13";"uMAX-uSOP_8";1;"DS1086L";;;
4;"U9,U8,U11,U10";"tssop-20";4;"74LXC245";;;
5;"U7";"tssop-20";1;"PCA9564";;;
6;"U6,U5";"TSOP48";2;"S29AL016J";;;
7;"U3,U4";"TSOP48";2;"AS6C3216";;;
8;"U2";"TQFP144";1;"XC95144XL-10TQG144C";;;
9;"C7,C40,C41";"SM1210L";3;"1uF";;;
10;"C21,C6";"SM0603_Capa";2;"0.01uF";;;
11;"C22,C4,C9,C8,C11,C10,C12,C15,C19,C16,C17,C18,C13,C14,C26,C25,C24,C23,C32,C31,C30,C33,C34,C35,C36,C37,C38,C39";"SM0603_Capa";28;"100nF";;;
12;"C5";"SM0603_Capa";1;"0.1uF";;;
13;"C1,C27";"SM0603_Capa";2;"0.22uF";;;
14;"C3,C29";"SM0603_Capa";2;"220pF";;;
15;"R1";"SM0603";1;"100";;;
16;"R8,R7,R4,R5";"SM0603";4;"4k7";;;
17;"R2,R3,R6";"SM0603";3;"k22";;;
18;"U1";"PQFP132M";1;"MC68030FE";;;
19;"J5";"PIN_ARRAY_4x1";1;"I2C_EXT";;;
20;"JP2";"PIN_ARRAY_3X1";1;"LOGIC CLK";;;
21;"JP1";"PIN_ARRAY_3X1";1;"CPU CLK";;;
22;"JP3";"PIN_ARRAY_3X1";1;"CLK SPREAD";;;
23;"J4";"PIN_ARRAY_2X1";1;"CONN_2";;;
24;"J3";"PIN_ARRAY-6X1";1;"XILINX_JTAG";;;
25;"U12";"MSOP_8";1;"MCP9801";;;
26;"D3,D2,D1";"LED-0805";3;"LED";;;
27;"U15";"DPAK3";1;"MCP1826S";;;
28;"U14";"DIP-8__300";1;"XTAL_OSC_DIP8";;;
29;"C2,C28";"c_tant_B";2;"22uF";;;
30;"C20";"c_tant_B";1;"4,7uF";;;
31;"JP4";"PIN_ARRAY_3X1";1;"QFP/PGA";;;
32;"JP5";"PIN_ARRAY_3X1";1;"NoFlash/Flash";;;
33;"U19";"VQFP44";1;"XC9536XL-5VQG44C";;;
34;"CON1";"8817-200-170S-F";1;"A3000/A4000_LOCAL_BUS_SLOT";;;
35;"U20";"MSOP-8";1;"MCP9801";;;
36;"Hole_4mm,Hole_4mm,Hole_4mm,Hole_4mm";"hole_4mm";4;"P***";;;
37;",,,,,,,,,,,,,,,,,,,,,,,,,,,,,,,,,,,,,,,,,,,,,,,,,,,,,,,,,,,,,,,,,,,,,,,,,,,,,,,,,,,,,,,,";"PINTST_0.8";89;"";;;
38;"";"LOGO";1;"";;;
